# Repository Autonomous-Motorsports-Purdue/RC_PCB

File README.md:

# RC_PCB
Printed circuit board for RC control and E-Stop

Should look something like this: [link](https://www.instructables.com/DIY-Game-Controller/)

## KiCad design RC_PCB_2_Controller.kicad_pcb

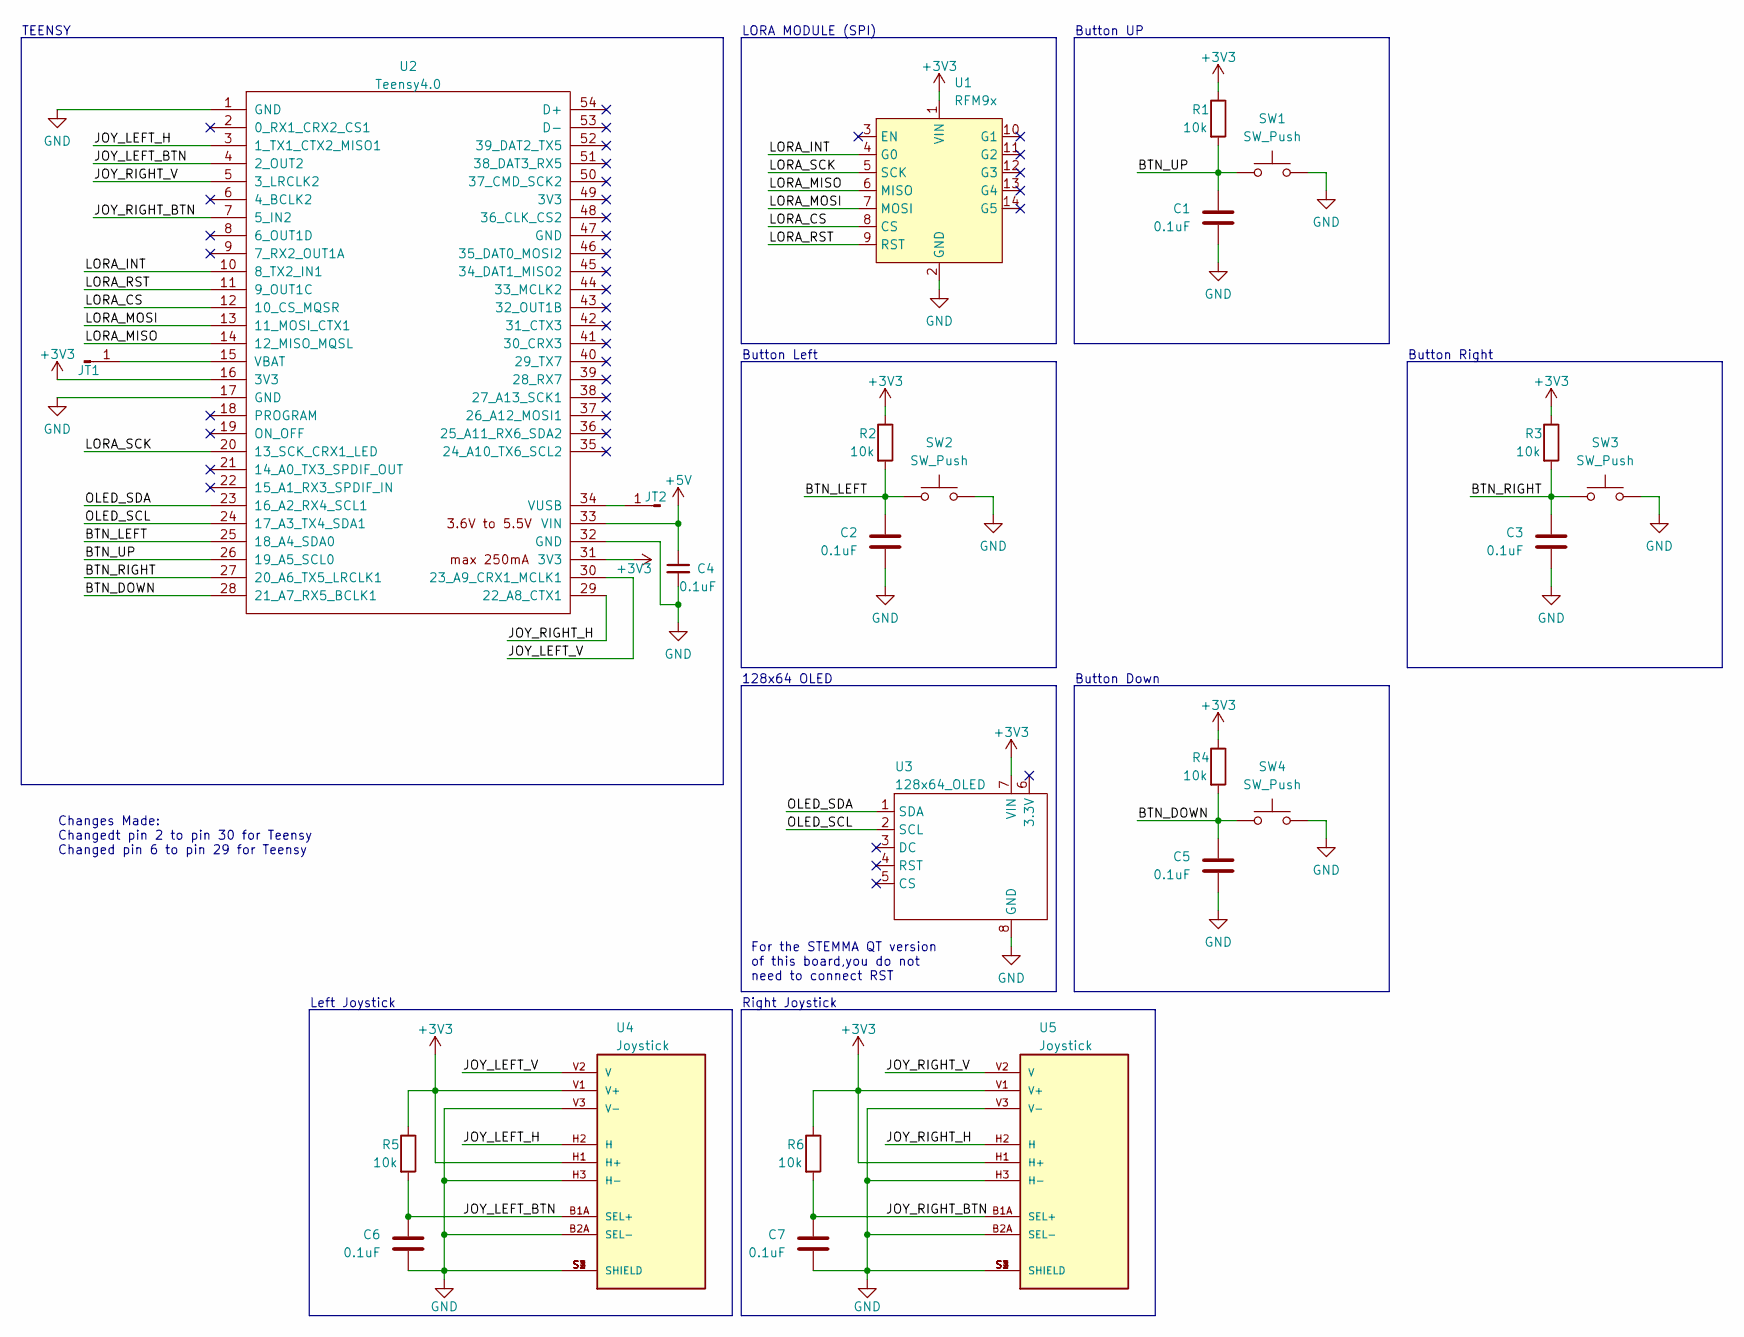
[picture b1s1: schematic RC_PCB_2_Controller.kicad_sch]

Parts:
C1, C2, C3, C4, C5, C6, C7: 0.1uF; C_0805_2012Metric_Pad1.18x1.45mm_HandSolder
JT1, JT2: Conn_01x01_Male; PinHeader_1x01_P2.54mm_Vertical
R1, R2, R3, R4, R5, R6: 10k; R_0805_2012Metric_Pad1.20x1.40mm_HandSolder
SW1, SW2, SW3, SW4: SW_Push; SW_PUSH-12mm
U1: RFM9x; RFM9x_Adafruit
U2: Teensy4.0; Teensy40
U3: 128x64_OLED
U4, U5: Joystick; XDCR_COM-09032; PARTREV N/A

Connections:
+3V3: R1.1, R2.1, R3.1, R4.1, R5.1, R6.1, U1.1 (VIN), U2.16 (3V3), U2.31 (3V3), U3.7 (VIN), U4.H1 (H+), U4.V1 (V+), U5.H1 (H+), U5.V1 (V+)
+5V: C4.1, U2.33 (VIN)
/BTN_DOWN: C5.1, R4.2, SW4.2, U2.28 (21_A7_RX5_BCLK1)
/BTN_LEFT: C2.1, R2.2, SW2.2, U2.25 (18_A4_SDA0)
/BTN_RIGHT: C3.1, R3.2, SW3.2, U2.27 (20_A6_TX5_LRCLK1)
/BTN_UP: C1.1, R1.2, SW1.2, U2.26 (19_A5_SCL0)
/JOY_LEFT_BTN: C6.1, R5.2, U2.4 (2_OUT2), U4.B1A (SEL+), U4.B1B
/JOY_LEFT_H: U2.3 (1_TX1_CTX2_MISO1), U4.H2 (H)
/JOY_LEFT_V: U2.30 (23_A9_CRX1_MCLK1), U4.V2 (V)
/JOY_RIGHT_BTN: C7.1, R6.2, U2.7 (5_IN2), U5.B1A (SEL+), U5.B1B
/JOY_RIGHT_H: U2.29 (22_A8_CTX1), U5.H2 (H)
/JOY_RIGHT_V: U2.5 (3_LRCLK2), U5.V2 (V)
/LORA_CS: U1.8 (CS), U2.12 (10_CS_MQSR)
/LORA_INT: U1.4 (G0), U2.10 (8_TX2_IN1)
/LORA_MISO: U1.6 (MISO), U2.14 (12_MISO_MQSL)
/LORA_MOSI: U1.7 (MOSI), U2.13 (11_MOSI_CTX1)
/LORA_RST: U1.9 (RST), U2.11 (9_OUT1C)
/LORA_SCK: U1.5 (SCK), U2.20 (13_SCK_CRX1_LED)
/OLED_SCL: U2.24 (17_A3_TX4_SDA1), U3.2 (SCL)
/OLED_SDA: U2.23 (16_A2_RX4_SCL1), U3.1 (SDA)
GND: C1.2, C2.2, C3.2, C4.2, C5.2, C6.2, C7.2, SW1.1, SW2.1, SW3.1, SW4.1, U1.2 (GND), U2.1 (GND), U2.17 (GND), U2.32 (GND), U3.8 (GND), U4.B2A (SEL-), U4.B2B, U4.H3 (H-), U4.S1 (SHIELD), U4.S2 (SHIELD), U4.S3 (SHIELD), U4.S4 (SHIELD), U4.V3 (V-), U5.B2A (SEL-), U5.B2B, U5.H3 (H-), U5.S1 (SHIELD), U5.S2 (SHIELD), U5.S3 (SHIELD), U5.S4 (SHIELD), U5.V3 (V-)
unnamed: JT1.1, U2.15 (VBAT)
unnamed: JT2.1, U2.34 (VUSB)

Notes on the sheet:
Right Joystick
Button Down
For the STEMMA QT version of this board,you do not need to connect RST
LORA MODULE (SPI)
Changes Made: Changedt pin 2 to pin 30 for Teensy Changed pin 6 to pin 29 for Teensy
Button Left
Button Right
Button UP
128x64 OLED
TEENSY
Left Joystick

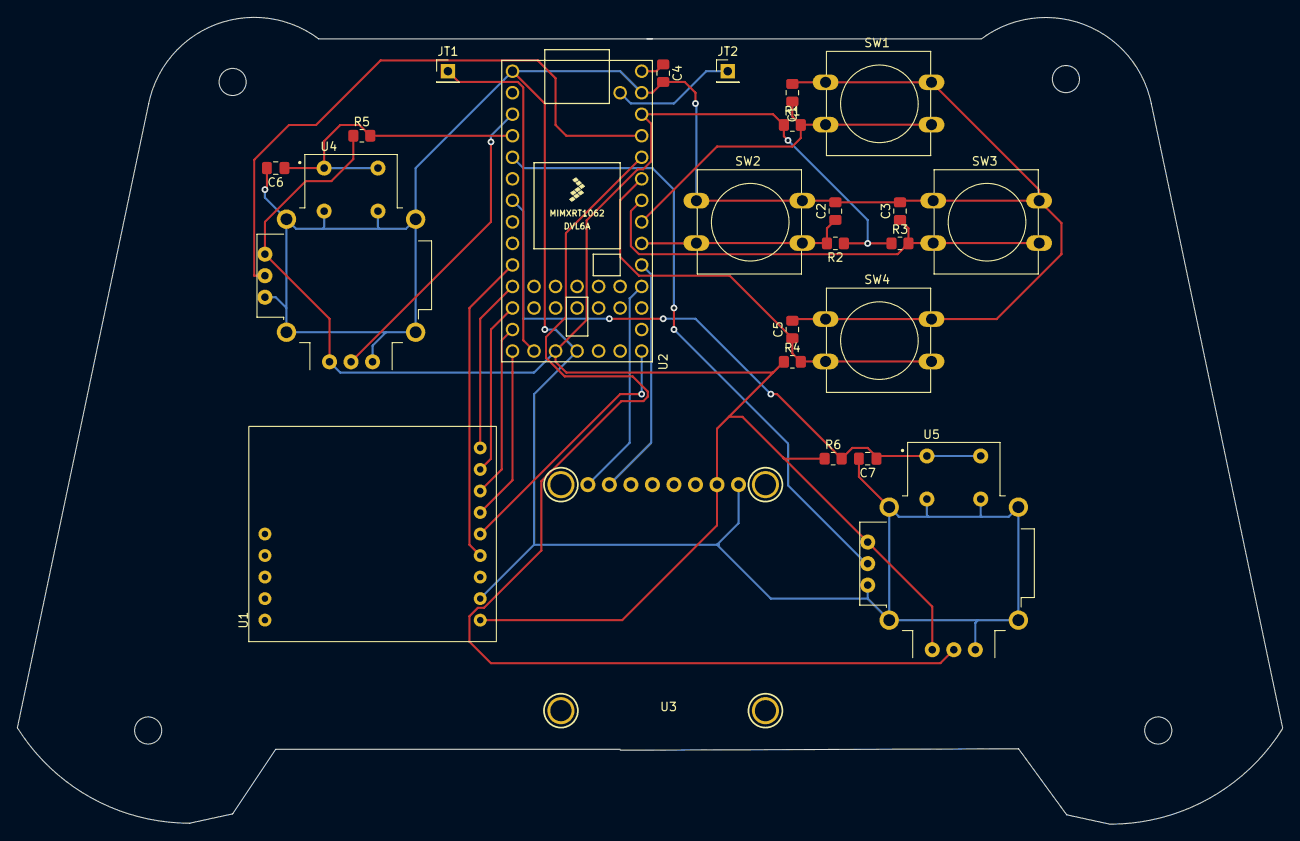
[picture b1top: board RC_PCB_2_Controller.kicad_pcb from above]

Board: 2 copper layers, 149.3 x 95.2 mm, 29 parts (1 on the bottom side), 23 nets.

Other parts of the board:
H3, H3#2, H3#3, H3#4: MountingHole; MountingHole_3.2mm_M3
U2#2: Logo

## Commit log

2023-03-06 Schematic completed except for OLED display
2023-03-07 Schematic almost done, PCB Layout started
2023-03-20 fixed lcd footprint
2023-03-21 initial layout complete
2023-03-27 completed drc, added amp logo, generated gerbers
2023-03-28 updated oled footprint
2023-10-29 Delete RC_PCB.kicad_pro
    Create New PCB
2023-10-29 Delete RC_PCB.kicad_pcb
    Made New PCB
2023-10-29 Delete RC_PCB.kicad_prl
    Made New PCB
2023-10-29 Delete RC_PCB.kicad_sch
    Made New PCB
2023-10-29 Begin STM32 migration
